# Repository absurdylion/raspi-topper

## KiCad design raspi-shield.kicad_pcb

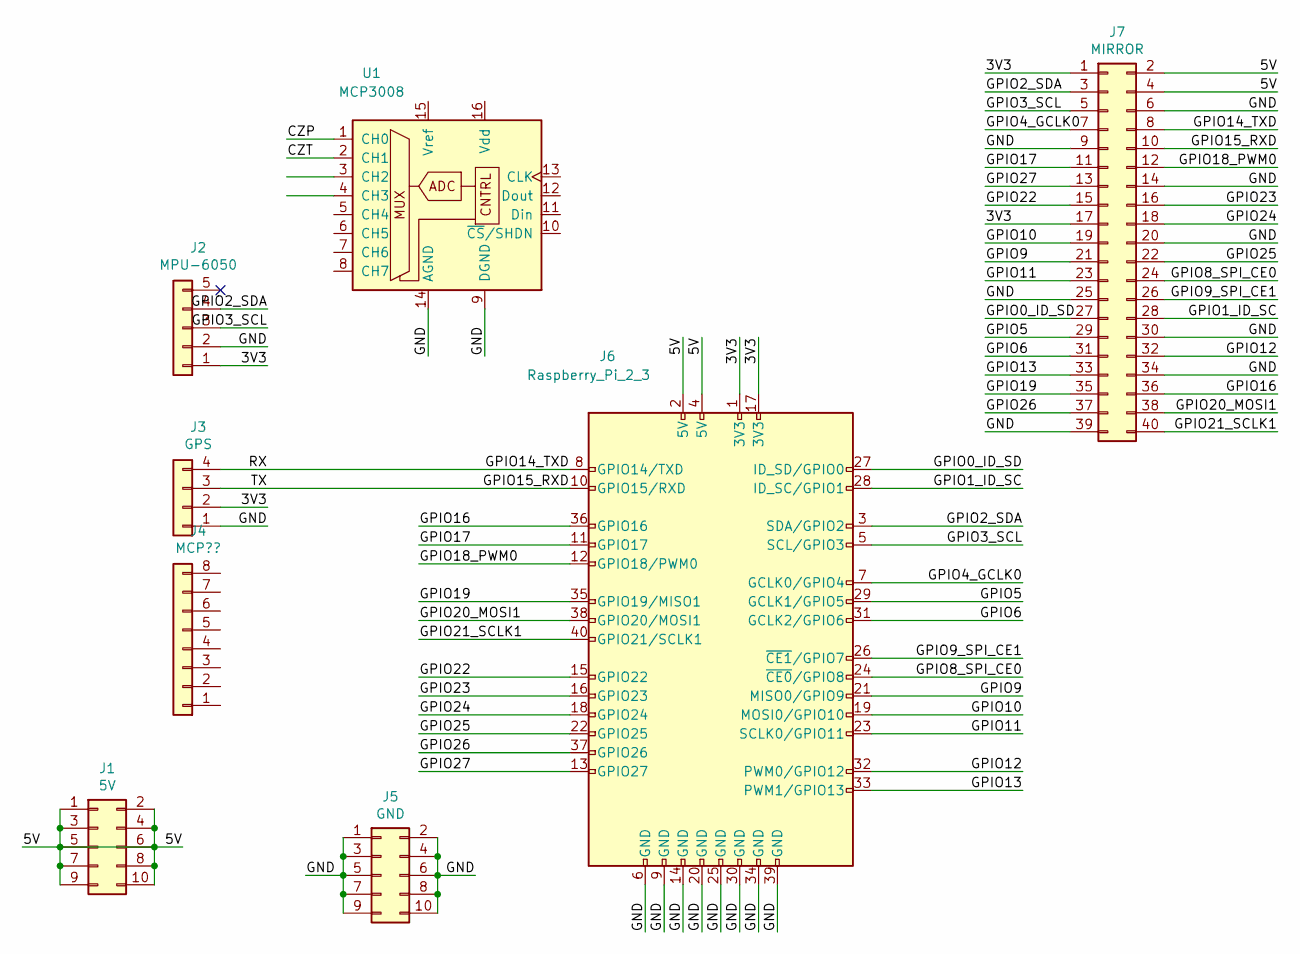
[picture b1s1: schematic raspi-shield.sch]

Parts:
J1: 5V; PinHeader_2x05_P2.54mm_Vertical
J2: MPU-6050; PinSocket_1x05_P2.54mm_Vertical
J3: GPS; PinSocket_1x04_P2.54mm_Vertical
J4: MCP??; PinSocket_2x04_P2.54mm_Vertical
J5: GND; PinHeader_2x05_P2.54mm_Vertical
J6: Raspberry_Pi_2_3; PinSocket_2x20_P2.54mm_Vertical
J7: MIRROR; PinHeader_2x20_P2.54mm_Vertical
U1: MCP3008; DIP-16_W10.16mm

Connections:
/3V3: J2.1, J3.2, J6.1 (3V3), J6.17 (3V3), J7.1, J7.17
/5V: J1.1, J1.2, J1.3, J1.4, J1.5, J1.6, J1.7, J1.8, J1.9, J1.10, J6.2 (5V), J6.4 (5V), J7.2, J7.4
/CZP: U1.1 (CH0)
/CZT: U1.2 (CH1)
/GND: J2.2, J3.1, J5.1, J5.2, J5.3, J5.4, J5.5, J5.6, J5.7, J5.8, J5.9, J5.10, J6.6 (GND), J6.9 (GND), J6.14 (GND), J6.20 (GND), J6.25 (GND), J6.30 (GND), J6.34 (GND), J6.39 (GND), J7.6, J7.9, J7.14, J7.20, J7.25, J7.30, J7.34, J7.39, U1.9 (DGND), U1.14 (AGND)
/GPIO0_ID_SD: J6.27 (ID_SD/GPIO0), J7.27
/GPIO1_ID_SC: J6.28 (ID_SC/GPIO1), J7.28
/GPIO2_SDA: J2.4, J6.3 (SDA/GPIO2), J7.3
/GPIO3_SCL: J2.3, J6.5 (SCL/GPIO3), J7.5
/GPIO4_GCLK0: J6.7 (GCLK0/GPIO4), J7.7
/GPIO5: J6.29 (GCLK1/GPIO5), J7.29
/GPIO6: J6.31 (GCLK2/GPIO6), J7.31
/GPIO8_SPI_CE0: J6.24 (~CE0~/GPIO8), J7.24
/GPIO9: J6.21 (MISO0/GPIO9), J7.21
/GPIO9_SPI_CE1: J6.26 (~CE1~/GPIO7), J7.26
/GPIO10: J6.19 (MOSI0/GPIO10), J7.19
/GPIO11: J6.23 (SCLK0/GPIO11), J7.23
/GPIO12: J6.32 (PWM0/GPIO12), J7.32
/GPIO13: J6.33 (PWM1/GPIO13), J7.33
/GPIO14_TXD: J3.4, J6.8 (GPIO14/TXD), J7.8
/GPIO15_RXD: J3.3, J6.10 (GPIO15/RXD), J7.10
/GPIO16: J6.36 (GPIO16), J7.36
/GPIO17: J6.11 (GPIO17), J7.11
/GPIO18_PWM0: J6.12 (GPIO18/PWM0), J7.12
/GPIO19: J6.35 (GPIO19/MISO1), J7.35
/GPIO20_MOSI1: J6.38 (GPIO20/MOSI1), J7.38
/GPIO21_SCLK1: J6.40 (GPIO21/SCLK1), J7.40
/GPIO22: J6.15 (GPIO22), J7.15
/GPIO23: J6.16 (GPIO23), J7.16
/GPIO24: J6.18 (GPIO24), J7.18
/GPIO25: J6.22 (GPIO25), J7.22
/GPIO26: J6.37 (GPIO26), J7.37
/GPIO27: J6.13 (GPIO27), J7.13

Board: 2 copper layers, 8 parts (1 on the bottom side), 31 nets, no tracks yet.

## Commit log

2022-12-30 opisy
